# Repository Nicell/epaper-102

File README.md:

# 1.02 inch e-ink Display Module

This is an open-source e-ink or e-paper display module that's only 19.5mm x 38.5mm.

This module is made for the Good Display GDEW0102T4 1.02 inch e-ink display, which [Waveshare resells](https://www.waveshare.com/product/displays/e-paper/epaper-3/1.02inch-e-paper-module.htm). This is a slimmed down version of the Waveshare module without the logic translation circuitry, which means this must be run at 3.3V.

## Ordering from JLCPCB and LCSC

This module is ready to be (almost fully) assembled. You'll need three files, `gerbers.zip`, `epaper-102-bom.csv`, and `epaper-102-bottom-pos.xlsx`.

1. Go to [JLCPCB.com](https://cart.jlcpcb.com/quote?orderType=1) quote page
2. Upload the `gerbers.zip` file to the quote page
3. Select any options you would like. PCB Color must be Green or Black and thickness must be 1.6mm
4. Check SMT Assembly under the PCB section
5. Select "Assemble bottom side"
6. Agree to terms and click Confirm
7. Add `epaper-102-bom.csv` as the BOM file and `epaper-102-bottom-pos.xlsx` as the CPL file on this page. Click Next
8. All parts on this page should be found automatically. Click next
9. Confirm placements look good (they should be fine) and click "Save to Cart"
10. Checkout when you're ready

## Ordering the display

You'll also need the actual 1.02 inch e-ink display to put in the module. You can order them from one of the following places:

 - [Waveshare](https://www.waveshare.com/product/displays/e-paper/epaper-3/1.02inch-e-paper.htm)
 - [AliExpress](https://www.aliexpress.com/item/4000504958641.html)
 - [Alibaba](https://goodlcd.en.alibaba.com/product/62454456237-807321088/1_inch_small_epaper_mini_eink_display_for_smart_watch.html)

I found AliExpress to be the cheapest in terms of display price and shipping, but you should check for yourself.

## Assembling

Once all your parts have arrived, you'll need to insert the display.

#### Connecting the display

Pull up on the FFC connector lever, and insert the display into the connector with the gold pins facing away from the PCB. Once it's all the way in, push the lever back down to lock it in place.

Now your module is all ready to go. You may want to use a bit of tape or adhesive to make sure the display sticks in place.

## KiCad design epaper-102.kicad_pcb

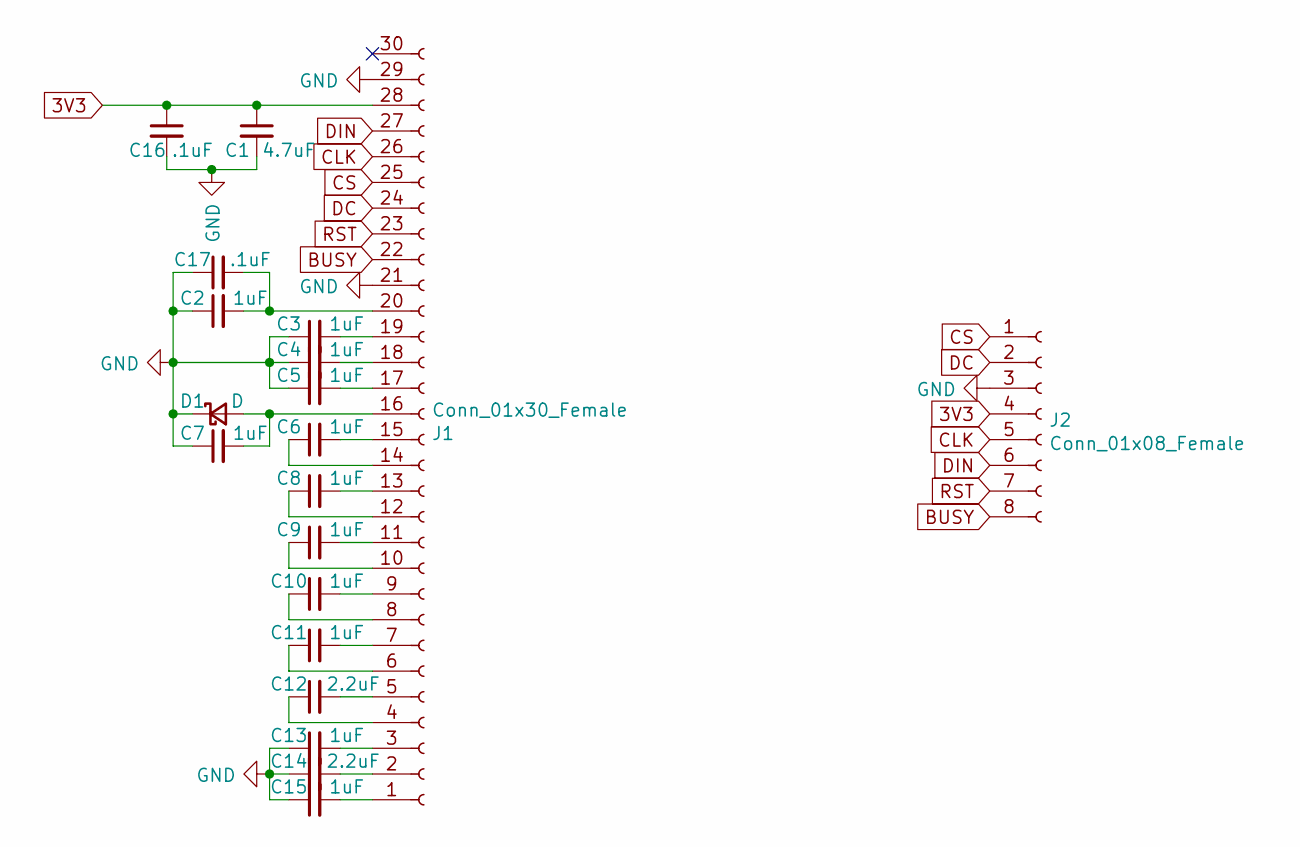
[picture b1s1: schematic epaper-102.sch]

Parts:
C1: 4.7uF; C_0402_1005Metric; LCSC C23733
C2, C3, C4, C5, C6, C7, C8, C9, C10, C11, C13, C15: 1uF; C_0402_1005Metric; LCSC C52923
C12, C14: 2.2uF; C_0603_1608Metric; LCSC C23630
C16, C17: .1uF; C_0402_1005Metric; LCSC C1525
D1: D; D_SOD-123; LCSC C8598
J1: Conn_01x30_Female; Hirose_FH12-30S-0.5SH_1x30-1MP_P0.50mm_Horizontal; LCSC C262294
J2: Conn_01x08_Female; PinHeader_1x08_P2.54mm_Vertical

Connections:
3V3: C1.1, C16.1, J1.28, J2.4
BUSY: J1.22, J2.8
CLK: J1.26, J2.5
CS: J1.25, J2.1
DC: J1.24, J2.2
DIN: J1.27, J2.6
GND: C1.2, C2.1, C3.1, C4.1, C5.1, C7.1, C13.1, C14.1, C15.1, C16.2, C17.1, D1.1 (K), J1.21, J1.29, J2.3
unnamed: C3.2, J1.19
unnamed: C4.2, J1.18
unnamed: C5.2, J1.17
unnamed: C6.1, J1.14
unnamed: C6.2, J1.15
unnamed: C7.2, D1.2 (A), J1.16
unnamed: C8.1, J1.12
unnamed: C8.2, J1.13
unnamed: C9.1, J1.10
unnamed: C9.2, J1.11
unnamed: C10.1, J1.8
unnamed: C10.2, J1.9
unnamed: C11.1, J1.6
unnamed: C11.2, J1.7
unnamed: C12.1, J1.4
unnamed: C12.2, J1.5
unnamed: C13.2, J1.3
unnamed: C14.2, J1.2
unnamed: C15.2, J1.1
unnamed: C2.2, C17.2, J1.20
RST: J1.23, J2.7

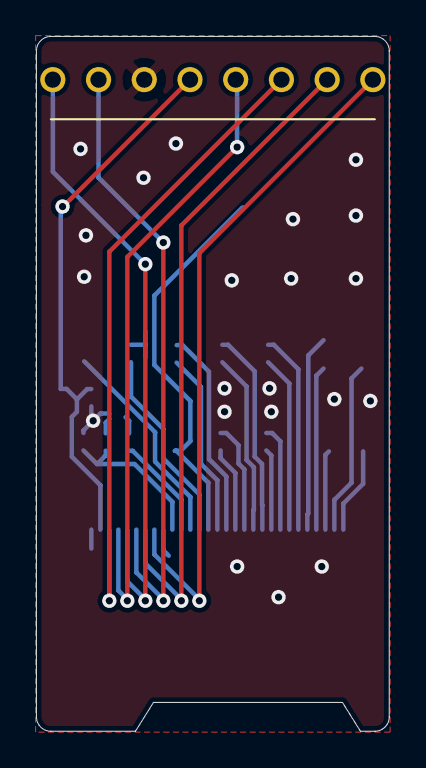
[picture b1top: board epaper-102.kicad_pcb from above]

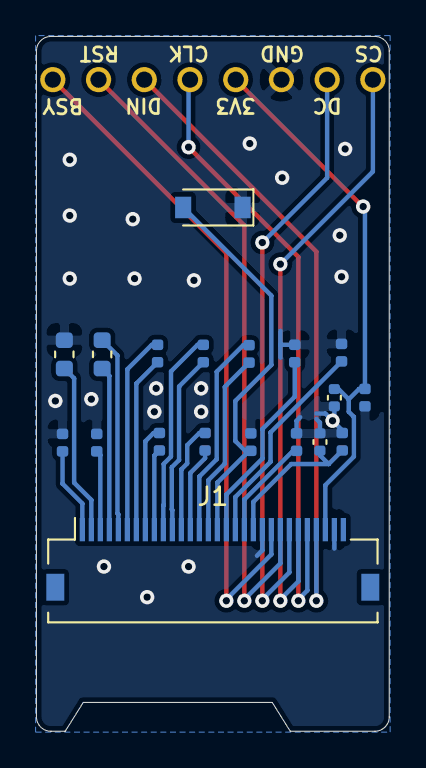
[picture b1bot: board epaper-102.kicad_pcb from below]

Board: 2 copper layers, 19.6 x 38.6 mm, 20 parts (20 on the bottom side), 28 nets.

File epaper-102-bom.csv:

"Item","Qty","Reference(s)","Value","LibPart","Footprint","Datasheet","LCSC"
"1","1","C1","4.7uF","Device:C_Small","Capacitor_SMD:C_0402_1005Metric","~","C23733"
"2","12","C2, C3, C4, C5, C6, C7, C8, C9, C10, C11, C13, C15","1uF","Device:C_Small","Capacitor_SMD:C_0402_1005Metric","~","C52923"
"3","2","C12, C14","2.2uF","Device:C_Small","Capacitor_SMD:C_0603_1608Metric","~","C23630"
"4","1","D1","D","Device:D_Schottky_Small","Diode_SMD:D_SOD-123","~","C8598"
"5","1","J1","Conn_01x30_Female","Connector:Conn_01x30_Female","Connector_FFC-FPC:Hirose_FH12-30S-0.5SH_1x30-1MP_P0.50mm_Horizontal","~","C262294"
"6","1","J2","Conn_01x08_Female","Connector:Conn_01x08_Female","Connector_PinHeader_2.00mm:PinHeader_1x08_P2.00mm_Vertical","~",""
"7","2","C16, C17","100nF","Device:C_Small","Capacitor_SMD:C_0402_1005Metric","~","C1525"

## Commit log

2021-04-22 Remove FCC soldering part
2021-04-23 Update position for FFC to match JLC SMT
2021-04-23 Clarify where the lever is
